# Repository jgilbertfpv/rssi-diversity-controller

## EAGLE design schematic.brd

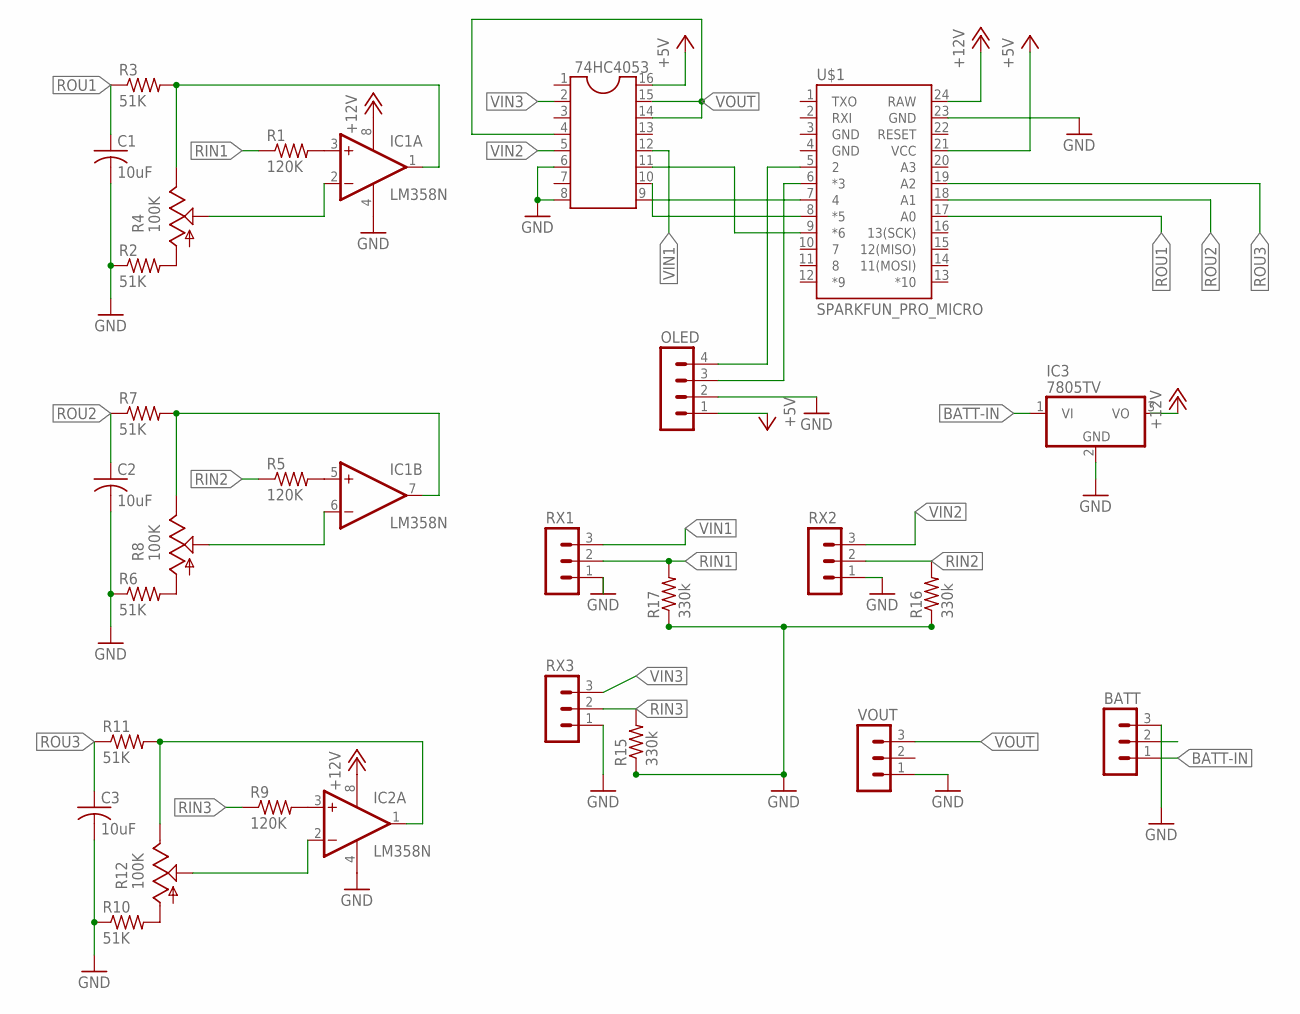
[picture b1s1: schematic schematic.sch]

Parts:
74HC4053: DIL16
BATT: MA03-1
C1, C2, C3: 10uF; C025-025X050
IC1, IC2: LM358N; DIL08
IC3: 7805TV; TO220V
OLED: MA04-1
R1, R5, R9: 120K; 0207/10
R2, R3, R6, R7, R10, R11: 51K; 0207/10
R4, R8, R12: 100K; S64W
R15, R16, R17: 330k; 0207/10
RX1, RX2, RX3: MA03-1
U$1: SPARKFUN_PRO_MICRO
VOUT: MA03-1

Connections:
+5V: 74HC4053.16, OLED.1, U$1.21 (VCC)
+12V: IC1.8 (V+), IC2.8 (V+), IC3.3 (VO), U$1.24 (RAW)
BATT-IN: BATT.1, IC3.1 (VI)
GND: 74HC4053.6, 74HC4053.8, BATT.3, C1.2, C2.2, C3.2, IC1.4 (V-), IC2.4 (V-), IC3.2 (GND), OLED.2, R2.1, R6.1, R10.1, R15.1, R16.1, R17.1, RX1.1, RX2.1, RX3.1, U$1.3 (GND), U$1.4 (GND), U$1.23 (GND), VOUT.1
unnamed: 74HC4053.11, U$1.9 (*6)
unnamed: 74HC4053.10, U$1.8 (*5)
unnamed: 74HC4053.9, U$1.7 (4)
unnamed: IC1.3 (+IN), R1.2
unnamed: IC1.1 (OUT), R3.2, R4.E
unnamed: IC1.2 (-IN), R4.S
unnamed: R2.2, R4.A
unnamed: OLED.4, U$1.5 (2)
unnamed: IC1.7 (OUT), R7.2, R8.E
unnamed: R6.2, R8.A
unnamed: IC1.6 (-IN), R8.S
unnamed: OLED.3, U$1.6 (*3)
unnamed: IC2.1 (OUT), R11.2, R12.E
unnamed: R10.2, R12.A
unnamed: IC2.2 (-IN), R12.S
unnamed: IC1.5 (+IN), R5.2
unnamed: IC2.3 (+IN), R9.2
RIN1: R1.1, R17.2, RX1.2
RIN2: R5.1, R16.2, RX2.2
RIN3: R9.1, R15.2, RX3.2
ROU1: C1.1, R3.1, U$1.17 (A0)
ROU2: C2.1, R7.1, U$1.18 (A1)
ROU3: C3.1, R11.1, U$1.19 (A2)
VIN1: 74HC4053.12, RX1.3
VIN2: 74HC4053.5, RX2.3
VIN3: 74HC4053.2, RX3.3
VOUT: 74HC4053.4, 74HC4053.14, 74HC4053.15, VOUT.3

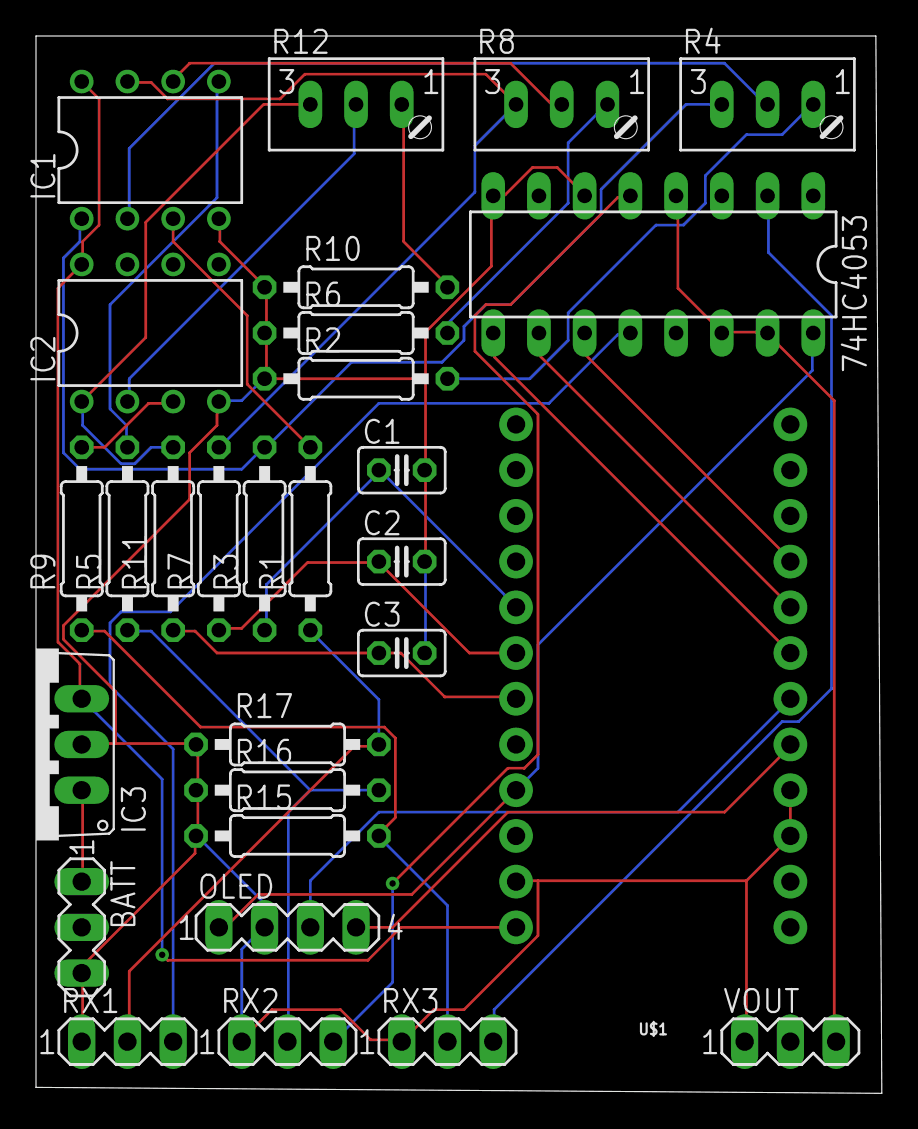
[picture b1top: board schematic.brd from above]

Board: 2 copper layers, 47.0 x 58.7 mm, 29 parts (0 on the bottom side), 31 nets.

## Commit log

2018-11-30 Update RSSI_Diversity_Controller.ino
    Pins changed to work with ssd1306 oled display and newer Arduino micro with the ATmega32u4 chip
2018-11-30 Update display.cpp
    ssd1306 OLED version
2018-11-30 SSD1306
    SSD1306 OLED support
2018-11-30 New board layout
    Smaller footprint and fixed to fit the newer Arduino micro with the 32u4 chip and SSD1306 OLED display
2020-01-27 Fix for 0-5v rssi
    RMRC 1.3 receivers use 0-5v for the rssi so changes have been made to accommodate the correct values.

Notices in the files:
parts and their libraries:
SparkFun-Boards: Licensing: Creative Commons ShareAlike 4.0 International - https://creativecommons.org/licenses/by-sa/4.0
